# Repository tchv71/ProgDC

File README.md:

## Программируемый дешифратор (MMU) для Пальмиры

Прототипом послужил программируемый дешифратор для Радио 86-РК, описанный в журналах "Радио" 1994, №3-5. 

[https://archive.radio.ru/web/1994/03/020/]: https://archive.radio.ru/web/1994/03/020/

Общая идея конструктива - плата программируемого дешифратора вставляется в сокет процессора, а процессор (возможно, в виде z80card) вставляется в панельку на плате ПД. Дополнительные сигналы к/от платы Пальмиры выводятся на штырьковый разъем на правом краю платы ПД.

Внесены следующие усовершенствования:

1. Устранена зависимость от значений системного регистра при программировании устройства по адресу 0FFh. В оригинальном устройстве запись по адресу 0FFh меняла и значение системного регистра, и ОЗУ дешифратора. Это налагало ограничение на значения, которые можно записать в порт 0FFh и усложняло программирование. Теперь эти порты схемотехнически разделены - если было предварительное чтение из порта 0FFh, запись будет в системный регистр, в противном случае - в ОЗУ дешифратора.
2. Используются все биты ОЗУ дешифратора, старшие 4 бита используются для расширения адреса системного ОЗУ. Поддерживается до 512К системного ОЗУ. Поддерживается 64 (максимум 128) кбайта ПЗУ.
3. Бит 4 ОЗУ дешифратора более не используется как признак "только чтение", вместо него используется значение 3 номера линии устройства.
4. Поддерживается бит 0 байта расширения конфигурации Пальмиры, включающий теневое ОЗУ по адресам 0-7FFFh.
5. Поддерживается до 4-х конфигураций дешифратора, которые выбираются битами 4-3 системного регистра. Таким образом, для того, чтобы изменить конфигурацию памяти, нет необходимости менять её постранично, можно запрограммировать новую конфигурацию заранее, а потом мгновенно применить её одной запись в порт 0FFh.
6. Поддерживается процессор Z80 в формате z80-card. 580ВМ80А также поддерживается, совместно с системным контроллером 580ВК38
7. Вместо микросхемы КР537РУ10 применена IDC6116SA45P как более быстродействующая, изменены тайминги сигнала записи в нее для повышения надежности записи.

## Системный регистр (in/out 0FFh)

|Бит|Обозначение|Биты управления режимом|
|-|-|-|
|7|Q7|Работа|
|6|Q6|Программирование портов ввода-вывода|
|5|Q5|Программирование конфигурации памяти|
|4||Биты выбора конфигурации (запись) Бит1|
|3||Биты выбора конфигурации (запись) Бит0|
|2||Биты выбора конфигурации (чтение) Бит1|
|1||Биты выбора конфигурации (чтение) Бит0|
|0||свободно|

Чтобы записать в системный регистр, надо сначала из него прочитать. Первая запись после чтения по адресу 0FFh будет в системный регистр, все последующие - в ОЗУ дешифратора (в режиме программирования) или в порт в рабочем режиме.

## Назначение линий выхода дешифратора ИД3:

|Номер линии|Адрес в Пальмире|Устройство|
|-|-|-|
|0|0C200h|ВВ55 контроллер клавиатуры|
|1|0C400h|ВВ55 дополнительный контроллер|
|2|0C000h|ВГ75 контроллер дисплея|
|3|-|ОЗУ только чтение|
|4|0E000h|ПЗУ|
|5|0000h|ОЗУ первые 32кб|
|6|0CC00h|ВИ53-1|
|7|0C600h|ВТ57/ВТ37|
|8|0C800h|ВИ53-2|
|9|||
|10|0D800h|ОЗУ ЗГ РУ10|
|11|0CE00h|Palmira ext. byte|
|12|0C300h|FT245R port|
|13|8000h|ОЗУ вторые 32кб|
|14|0CA00h|VDP TMS9918A|
|15|0F700h|Страница контроллеров RK60k|

Линия 15 задает положения страницы контроллеров RK60k размером 256 байт. Контроллеры имеют следующие фиксированные относительные адреса:

|Номер|Контроллер|Адрес|
|-|-|-|
|0|FDC |0F700h; 1793 floppy disk controller|
|1|INTR|0F720h; 8259 interrupt controller   |
|2|PSG1|0F740h; 8253 first	                |
|3|PSG2|0F760h; 8253 second	      	        |
|4|PPI |0F780h; 8255 fist		                |
|5|PPI2|0F7A0h; 8255 second	            	  |
|6|DISP|0F7C0h; 8275 display adapter	      |
|7|DMA |0F7E0h; 8257 DMA chip	    	        |

Поскольку одна конфигурация занимает 512 байт в ОЗУ дешифратора, появляется возможность хранить 4 конфигурации и мгновенно переключать их битами 3 и 4 системного регистра.

## ПЗУ 556РТ4

| Бит адреса | Сигнал |
| ---------- | ------ |
| A3         | Q7     |
| A2         | Q6     |
| A1         | Q5     |
| A0         | In/Out |

## Ошибки в печатных платах:

### Версия 1.4:

1. На микросхему D10 6116SA45P не заведено питание и земля.
2. Вывод 8 В14.3 К555ЛА3 должен быть подключен к выводу 15 D9 КР556РТ4, а вывод 4 D9 - к земле.

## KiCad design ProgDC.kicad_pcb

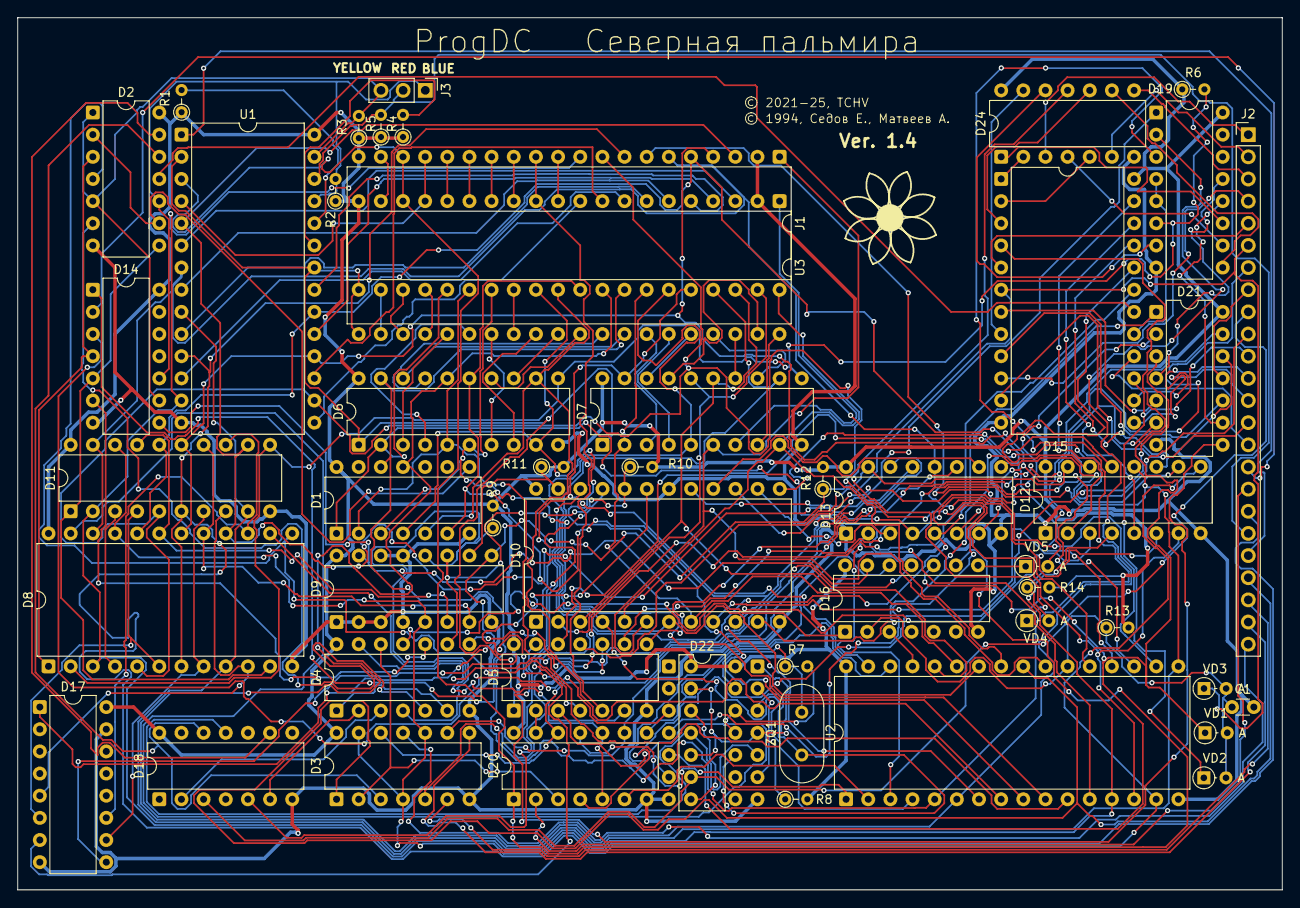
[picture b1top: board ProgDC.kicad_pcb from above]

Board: 2 copper layers, 145.0 x 100.0 mm, 51 parts (1 on the bottom side), 179 nets.

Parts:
C1: 470; C_Disc_D3.0mm_W1.6mm_P2.50mm
D1: K155LA2; DIP-14_W7.62mm
D2, D4, D16: 133LL1; DIP-14_W7.62mm
D3, D20, D24: 133LI1; DIP-14_W7.62mm
D5, D22: 133LN1; DIP-14_W7.62mm
D6, D7, D11: 1533ИР22; DIP-20_W7.62mm
D8: К589ИР12; DIP-24_W15.24mm
D9: КР556РТ4; DIP-16_W7.62mm
D10: КР537РУ10; DIP-24_W15.24mm
D12, D13: K589АП16; DIP-16_W7.62mm
D14: 133LA3; DIP-14_W7.62mm
D15: 155ID3; DIP-24_W15.24mm
D17: КР1533КП11; DIP-16_W7.62mm
D18, D23: 555TM2; DIP-14_W7.62mm
D19: 74AC138(COMB); DIP-16_W7.62mm
D21: 74HC86N; DIP-14_W7.62mm
J1: Conn_02x20_Counter_Clockwise_MountingPin; DIP-40_W15.24mm
J2: Conn_01x24_Pin; PinHeader_1x24_P2.54mm_Vertical
J3: Conn_01x03_Pin; PinHeader_1x03_P2.54mm_Vertical
R1, R2, R3, R4, R5, R6, R9, R10, R11, R12, R13, R14: R0125; R_Axial_DIN0204_L3.6mm_D1.6mm_P2.54mm_Vertical
R7, R8: R0125H; R_Axial_DIN0204_L3.6mm_D1.6mm_P2.54mm_Vertical
U1: KR580VK28; DIP-28_W15.24mm
U2: 628512; DIP-32_W15.24mm
U3: CPU; DIP-40_W15.24mm
VD1, VD2, VD3, VD4, VD5: 1N4148; D_DO-34_SOD68_P2.54mm_Vertical_AnodeUp
ZQ1: QUARTZ; Crystal_HC18-U_Vertical

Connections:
+5V: D1.14 (VCC), D2.14 (VCC), D3.14 (VCC), D4.14 (VCC), D5.14 (VCC), D6.20 (VCC), D7.20 (VCC), D8.24 (VCC), D9.16 (+5V), D10.24 (VCC), D11.20 (VCC), D12.16 (VCC), D13.16 (VCC), D14.14 (VCC), D15.24 (VCC), D16.14 (VCC), D17.16 (VCC), D18.14 (VCC), D19.16 (VCC), D20.14 (VCC), D21.14 (VCC), D22.14 (VCC), D23.14 (VCC), D24.14 (VCC), J1.20, R1.1 (TOP), R2.1 (TOP), R3.1 (TOP), R4.1 (TOP), R5.1 (TOP), R6.1 (TOP), R8.2, R9.2 (BOT), R10.2 (BOT), R11.2 (BOT), R12.2 (BOT), R13.2 (BOT), R14.2 (BOT), U1.28 (VCC), U2.32 (VCC), U3.20 (VCC)
/8MHZ: D18.11 (C), D23.5 (Q), D23.11 (C)
/"1": D6.11 (PE), D7.11 (PE), D8.2 (MD), D11.11 (PE), D19.6 (E1), R6.2 (BOT)
/+12V: J1.28, U3.28 (+12V)
/-5V: J1.11, U3.11 (-5V)
/A0: D6.3 (D0), U3.25 (A0)
/A1: D6.4 (D1), U3.26 (A1)
/A2: D6.7 (D2), U3.27 (A2)
/A3: D6.8 (D3), U3.29 (A3)
/A4: D6.13 (D4), U3.30 (A4)
/A5: D6.14 (D5), U3.31 (A5)
/A6: D6.17 (D6), U3.32 (A6)
/A7: D6.18 (D7), U3.33 (A7)
/A8: D7.3 (D0), U3.34 (A8)
/A9: D7.4 (D1), U3.35 (A9)
/A10: D7.7 (D2), U3.1 (A10)
/A11: D7.8 (D3), U3.40 (A11)
/A12: D7.13 (D4), U3.37 (A12)
/A13: D7.14 (D5), U3.38 (A13)
/A14: D7.17 (D6), U3.39 (A14)
/A15: D7.18 (D7), U3.36 (A15)
/AB0: D1.1, D6.2 (Q0), J1.25, U2.12 (A0)
/AB1: D1.2, D6.5 (Q1), J1.26, U2.11 (A1)
/AB2: D1.3, D6.6 (Q2), J1.27, U2.10 (A2)
/AB3: D1.4, D6.9 (Q3), J1.29, U2.9 (A3)
/AB4: D1.5, D6.12 (Q4), J1.30, U2.8 (A4)
/AB5: D1.6, D6.15 (Q5), D19.1 (0), J1.31, U2.7 (A5)
/AB6: D1.11, D6.16 (Q6), D19.2 (1), J1.32, U2.6 (A6)
/AB7: D1.12, D6.19 (Q7), D19.3 (2), J1.33, U2.5 (A7)
/AB8: D7.2 (Q0), D10.8 (A10), J1.34, U2.27 (A8)
/AB9: D7.5 (Q1), D10.7 (A9), J1.35, U2.26 (A9)
/AB10: D7.6 (Q2), D10.6 (A8), J1.1, U2.23 (A10)
/AB11: D7.9 (Q3), D10.5 (A7), J1.40, U2.25 (A11)
/AB12: D7.12 (Q4), D10.4 (A6), J1.37, U2.4 (A12)
/AB13: D7.15 (Q5), D10.3 (A5), J1.38, U2.28 (A13)
/AB14: D7.16 (Q6), D10.2 (A4), J1.39
/AB15: D7.19 (Q7), D10.1 (A3), J1.36, U2.31 (A15)
/ARR16: D20.6 (Y), U2.2 (A16)
/ARR17: D20.8 (Y), U2.30 (A17)
/ARR18: D20.11 (Y), U2.1 (A18)
/C1: J1.22, U3.22 (C1)
/C2: J1.15, U3.15 (C2)
/C800_VI53_2: D5.13 (A), D21.8 (Y)
/CLK: D18.3 (C), D23.9 (Q), J2.9
/CS_RAMR: D16.12 (A), D22.6 (Y)
/D0: U1.15 (D0), U3.10 (D0)
/D1: U1.17 (D1), U3.9 (D1)
/D2: U1.12 (D2), U3.8 (D2)
/D3: U1.10 (D3), U3.7 (D3)
/D4: U1.6 (D4), U3.3 (D4)
/D5: U1.19 (D5), U3.4 (D5)
/D6: U1.21 (D6), U3.5 (D6)
/D7: U1.8 (D7), U3.6 (D7)
/DB0: D8.3 (D0), D11.2 (Q0), D12.4 (DI0), J1.10, U1.13 (DB0), U2.13 (D0)
/DB1: D8.5 (D1), D11.5 (Q1), D12.7 (DI1), J1.9, U1.16 (DB1), U2.14 (D1)
/DB2: D8.7 (D2), D11.6 (Q2), D12.9 (DI2), J1.8, U1.11 (DB2), U2.15 (D2)
/DB3: D8.9 (D3), D11.9 (Q3), D12.12 (DI3), J1.7, U1.9 (DB3), U2.17 (D3)
/DB4: D8.16 (D4), D11.12 (Q4), D13.4 (DI0), J1.3, U1.5 (DB4), U2.18 (D4)
/DB5: D8.18 (D5), D11.15 (Q5), D13.7 (DI1), J1.4, U1.18 (DB5), U2.19 (D5)
/DB6: D8.20 (D6), D11.16 (Q6), D13.9 (DI2), J1.5, U1.20 (DB6), U2.20 (D6)
/DB7: D8.22 (D7), D11.19 (Q7), D13.12 (DI3), J1.6, U1.7 (DB7), U2.21 (D7)
/DBIN: J1.17, U1.4 (DBIN), U3.17 (RC)
/HLD: J1.13, U3.13 (HLD)
/HLDA: D5.1 (A), D6.1 (~EO), D7.1 (~EO), J1.21, U1.2 (HLDA), U1.22 (BUSEN), U3.21 (HLDA)
/INT: J1.14, U3.14 (INT)
/INTE: J1.16, U3.16 (INTE)
/P0: D4.4 (A), D9.12 (D0), R9.1 (TOP)
/P1: D4.9 (A), D9.11 (D1), D10.20 (~OE), R10.1 (TOP)
/P2: D9.10 (D2), D10.23 (A2), R11.1 (TOP)
/P3: D9.9 (D3), D12.15 (~CE), D13.15 (~CE), D17.1 (SEL), R12.1 (TOP)
/Q0: D8.4 (Q0), D11.3 (D0)
/Q1: D8.6 (Q1), D11.4 (D1), D17.6 (2B)
/Q2: D8.8 (Q2), D11.7 (D2), D17.10 (3B)
/Q3: D8.10 (Q3), D11.8 (D3), D17.5 (2A)
/Q4: D8.15 (Q4), D11.13 (D4), D17.11 (3A)
/Q5: D8.17 (Q5), D9.7 (A2), D11.14 (D5)
/Q6: D8.19 (Q6), D9.6 (A1), D11.17 (D6)
/Q7: D3.4 (A), D3.10 (B), D3.13 (B), D8.21 (Q7), D9.5 (A0), D11.18 (D7), J2.18
/R0: D12.2 (DO0), D15.23 (1)
/R1: D12.5 (DO1), D15.22 (2)
/R2: D12.11 (DO2), D15.21 (4)
/R3: D12.14 (DO3), D15.20 (8)
/R4: D13.2 (DO0), U2.3 (A14)
/R5: D3.5 (B), D13.5 (DO1), D21.1 (A)
/R6: D3.9 (A), D13.11 (DO2), D20.9 (A)
/R7: D3.12 (A), D13.14 (DO3), D20.12 (A)
/R8: D14.3 (Y), D22.3 (A)
/RAM_SEL: D14.2 (B), J2.16
/RDY: J1.23, U3.23 (RDY)
/RESET: D5.5 (A), J1.12, U3.12 (RST)
/ROM_A13: D3.6 (Y), J2.22
/ROM_A14: D3.8 (Y), J2.23
/ROM_A15: D3.11 (Y), J2.24
/STSTB: J2.20, U1.1 (STSTB)
/SYN: J1.19, U3.19 (SYN)
/WI: J1.24, U3.24 (WI)
/~A_FF: D1.8, D2.2 (B), D2.9 (A)
/~C100_SD_CNTR: D15.10 (9), J2.4
/~C200_PPI1_: D24.3 (Y), J2.1
/~C200_PPI1: D15.1 (0), D24.2 (B)
/~C300: D15.14 (12), J2.13
/~C400_PPI2_: D24.6 (Y), J2.2
/~C400_PPI2: D15.2 (1), D24.5 (B)
/~C500_VDP: D15.16 (14), J2.15
/~C800_VI53_2_: D5.12 (Y), J2.10
/~C800_VI53_2: D15.9 (8), D21.10 (B)
/~CC00_VI53_1_: D5.8 (Y), J2.7
/~CC00_VI53_1: D15.7 (6), D21.5 (B)
/~CE00: D15.13 (11), J2.12
/~CS_628512: C1.1, D16.2 (B), R13.1 (TOP), U2.22 (CS), VD1.2 (A), VD2.2 (A), VD3.2 (A)
/~CS_D800: D15.11 (10), J2.14
/~CS_DMA_2: D21.11 (Y), J2.8
/~CS_DMA_: D24.11 (Y), VD4.1 (K)
/~CS_DMA: D15.8 (7), D24.13 (B)
/~CS_RAMR: D15.4 (3), D16.10 (B), D22.5 (A), VD1.1 (K)
/~CS_ROM: D15.5 (4), J2.5
/~CS_SRAM_8000: D15.15 (13), J2.11, VD2.1 (K)
/~CS_VG75_: D24.8 (Y), J2.3
/~CS_VG75: D15.3 (2), D24.10 (B)
/~D15_CS1: D4.8 (Y), D15.19 (&C)
/~D15_CS2: D2.11 (Y), D15.18 (C)
/~F700: D15.17 (15), D19.4 (~E2), D19.5 (~E3)
/~INTA: R4.2 (BOT), U1.23 (INTA)
/~I/OR: D2.10 (B), D14.10 (B), J3.1, R2.2 (BOT), U1.25 (I/OR)
/~I/OW: D2.1 (A), D2.5 (B), D14.9 (A), J3.3, R3.2 (BOT), U1.27 (I/OW)
/~MEMR: R1.2 (BOT), U1.24 (MEMR)
/~MEMW_VT57: D20.2 (B), J2.17
/~MEMW: J2.19, J3.2, R5.2 (BOT), U1.26 (MEMW)
/~MWR: D3.2 (B), D4.12 (A), D20.3 (Y)
/~RAM_MAIN: D5.11 (A), D15.6 (5), J2.6, VD3.1 (K)
/~RD: D3.1 (A), J2.21, U2.24 (RD)
/~RESET: D5.6 (Y), D8.14 (RES)
/~WE_628512: D4.11 (Y), D16.1 (A)
/~WR: D16.9 (A), D20.1 (A), J1.18, U1.3 (WR), U3.18 (TR)
GND: C1.2, D1.7 (GND), D2.7 (GND), D3.7 (GND), D4.7 (GND), D5.7 (GND), D6.10 (GND), D7.10 (GND), D8.12 (GND), D9.1 (A6), D9.2 (A5), D9.3 (A4), D9.4 (A3), D9.8 (GND), D9.13 (~CS1), D9.14 (~CS2), D10.12 (GND), D10.18 (~CS), D11.10 (GND), D12.1 (~CS), D12.8 (GND), D13.1 (~CS), D13.8 (GND), D14.7 (GND), D15.12 (GND), D16.7 (GND), D17.8 (GND), D17.15 (~OE), D18.7 (GND), D19.8 (GND), D20.7 (GND), D21.7 (GND), D21.12 (A), D22.7 (GND), D23.7 (GND), D24.7 (GND), J1.2, U1.14 (GND), U2.16 (GND), U3.2 (GND)
unnamed: D2.4 (A), D5.4 (Y), D8.13 (CS2)
unnamed: D2.6 (Y), D4.5 (B)
unnamed: D4.1 (A), D4.6 (Y)
unnamed: D5.3 (A), D8.23 (S1)
unnamed: D10.19 (A0), D17.9 (3Y)
unnamed: D10.22 (A1), D17.7 (2Y)
unnamed: D10.9 (D0), D12.3 (DB0)
unnamed: D10.10 (D1), D12.6 (DB1)
unnamed: D10.11 (D2), D12.10 (DB2)
unnamed: D10.13 (D3), D12.13 (DB3)
unnamed: D10.14 (D4), D13.3 (DB0)
unnamed: D10.15 (D5), D13.6 (DB1)
unnamed: D10.16 (D6), D13.10 (DB2)
unnamed: D10.17 (D7), D13.13 (DB3)
unnamed: D10.21 (~WE), D18.5 (Q)
unnamed: D2.8 (Y), D8.11 (EV), D11.1 (~EO), D14.5 (B)
unnamed: D5.10 (Y), D14.1 (A)
unnamed: D2.3 (Y), D8.1 (CS1), D14.4 (A)
unnamed: D4.10 (B), D14.6 (Y)
unnamed: D9.15 (A7), D14.8 (Y), D16.13 (B)
unnamed: D16.3 (Y), U2.29 (WR)
unnamed: D16.8 (Y), VD5.1 (K)
unnamed: D4.13 (B), D16.11 (Y)
unnamed: D4.3 (Y), D18.2 (D)
unnamed: D4.2 (B), D18.6 (~Q)
unnamed: D2.12 (A), D3.3 (Y), D18.12 (D)
unnamed: D2.13 (B), D18.9 (Q)
unnamed: D19.12 (3), D21.9 (A)
unnamed: D19.11 (4), D24.1 (A)
unnamed: D19.10 (5), D24.4 (A)
unnamed: D19.9 (6), D24.9 (A)
unnamed: D20.4 (A), D21.3 (Y)
unnamed: D5.2 (Y), D20.5 (B), D20.10 (B), D20.13 (B)
unnamed: D21.2 (B), D22.4 (Y)
unnamed: D19.13 (2), D21.4 (A)
unnamed: D5.9 (A), D21.6 (Y)
unnamed: D21.13 (B), R14.1 (TOP), VD4.2 (A), VD5.2 (A)
unnamed: D22.11 (A), D22.12 (Y), R7.2
unnamed: D22.10 (Y), D23.3 (C), ZQ1.1
unnamed: D22.13 (A), R7.1, ZQ1.2
unnamed: D23.2 (D), D23.6 (~Q)
unnamed: D23.1 (~R), D23.4 (~S), D23.10 (~S), D23.13 (~R)
unnamed: D23.8 (~Q), D23.12 (D)
unnamed: D19.7, D24.12 (A)

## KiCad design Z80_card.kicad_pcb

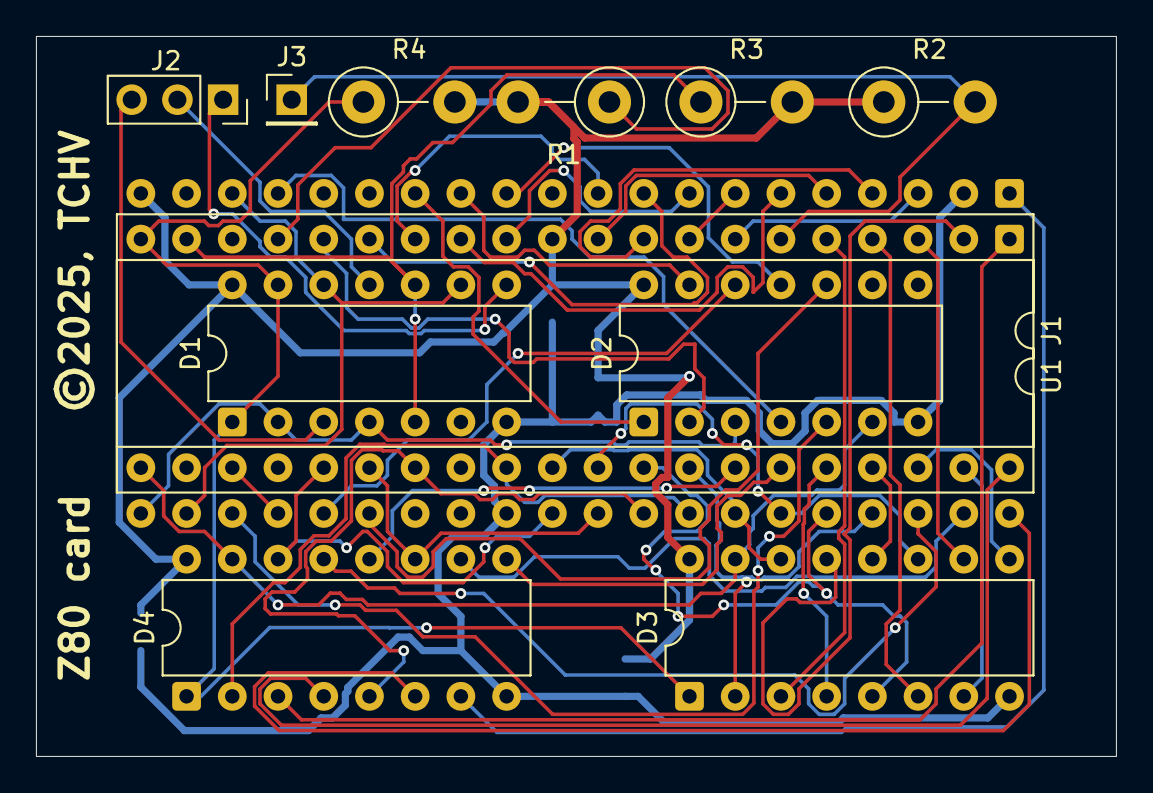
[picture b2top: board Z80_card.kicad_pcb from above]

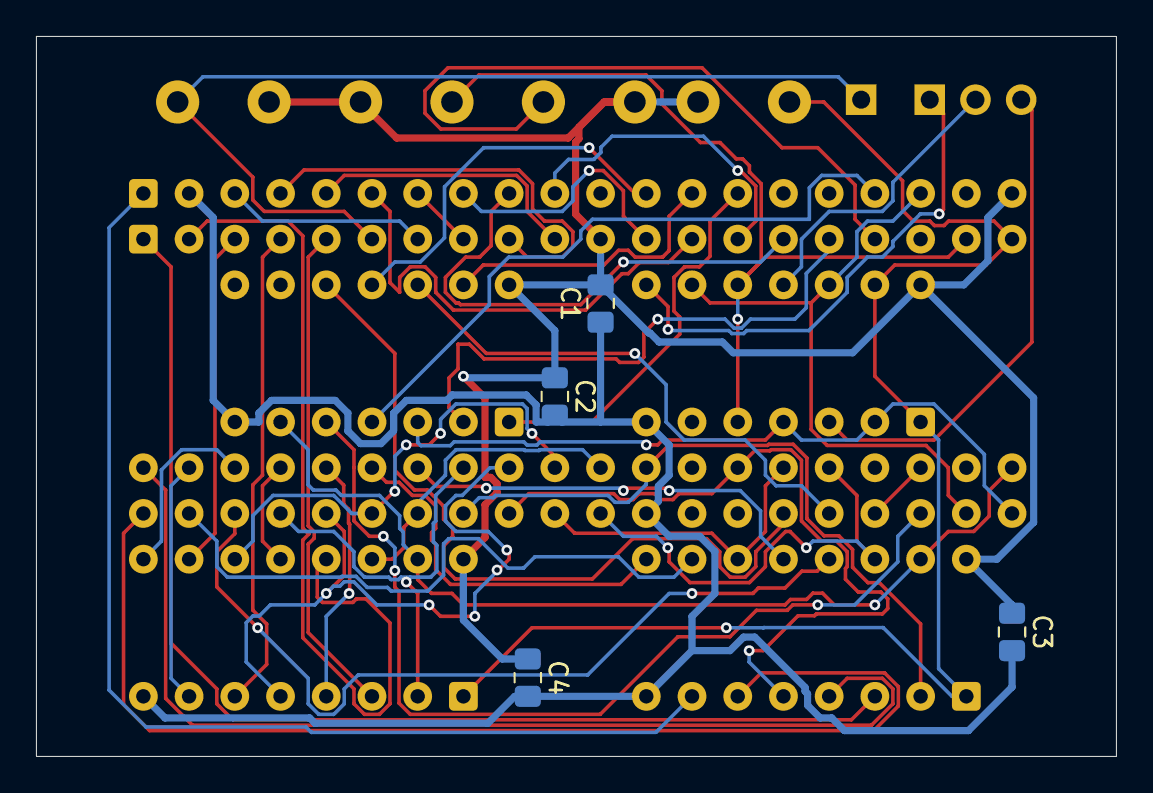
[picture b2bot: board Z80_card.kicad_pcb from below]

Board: 2 copper layers, 60.0 x 40.0 mm, 16 parts (4 on the bottom side), 53 nets.

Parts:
C1, C2, C3, C4: C; C_0805_2012Metric_Pad1.18x1.45mm_HandSolder
D1: 133LL1; DIP-14_W7.62mm
D2: 133LN1; DIP-14_W7.62mm
D3, D4: КР1533КП11; DIP-16_W7.62mm
J1: Conn_02x20_Counter_Clockwise_MountingPin; DIP-40_W15.24mm
J2: Conn_01x03_Pin; PinSocket_1x03_P2.54mm_Vertical
J3: Conn_01x01_Pin; PinHeader_1x01_P2.54mm_Vertical
R1, R2, R3, R4: R0125; R_Axial_DIN0411_L9.9mm_D3.6mm_P5.08mm_Vertical
U1: Z84C00-4SC; DIP-40_W15.24mm

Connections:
+5V: C1.2, C2.1, C3.1, C4.1, D1.14 (VCC), D2.14 (VCC), D3.16 (VCC), D4.16 (VCC), J1.20, R1.2 (BOT), R2.1 (TOP), R3.2 (BOT), R4.2 (BOT), U1.11 (VCC)
/A0: D4.14 (4A), J1.25, U1.30 (A0)
/A1: D4.11 (3A), J1.26, U1.31 (A1)
/A2: D4.5 (2A), J1.27, U1.32 (A2)
/A3: D4.2 (1A), J1.29, U1.33 (A3)
/A4: D3.14 (4A), J1.30, U1.34 (A4)
/A5: D3.11 (3A), J1.31, U1.35 (A5)
/A6: D3.5 (2A), J1.32, U1.36 (A6)
/A7: D3.2 (1A), J1.33, U1.37 (A7)
/A8: D4.12 (4Y), J1.34
/A9: D4.9 (3Y), J1.35
/A10: D4.7 (2Y), J1.1
/A11: D4.4 (1Y), J1.40
/A12: D3.12 (4Y), J1.37
/A13: D3.9 (3Y), J1.38
/A14: D3.7 (2Y), J1.39
/A15: D3.4 (1Y), J1.36
/BLUE: D1.3 (Y), J2.3
/CLK: J3.1, R2.2 (BOT), U1.6 (CLK)
/D0: J1.10, U1.14 (D0)
/D1: J1.9, U1.15 (D1)
/D2: J1.8, U1.12 (D2)
/D3: J1.7, U1.8 (D3)
/D4: J1.3, U1.7 (D4)
/D5: J1.4, U1.9 (D5)
/D6: J1.5, U1.10 (D6)
/D7: J1.6, U1.13 (D7)
/DBIN: D2.4 (Y), J1.17
/HLD: D2.13 (A), J1.13
/INT: D2.1 (A), J1.14
/RDY: J1.23, U1.24 (~WAIT)
/RED: D1.8 (Y), J2.1
/RESET: D2.11 (A), J1.12
/YELLOW: D1.11 (Y), J2.2
/_A8: D4.13 (4B), U1.38 (A8)
/_A9: D4.10 (3B), U1.39 (A9)
/_A10: D4.6 (2B), U1.40 (A10)
/_A11: D4.3 (1B), U1.1 (A11)
/_A12: D3.13 (4B), U1.2 (A12)
/_A13: D3.10 (3B), U1.3 (A13)
/_A14: D3.6 (2B), U1.4 (A14)
/_A15: D3.3 (1B), U1.5 (A15)
/_HLDA: D2.6 (Y), D3.15 (~OE), D4.15 (~OE), J1.21
/~RESET: D2.10 (Y), U1.26 (~RESET)
/~WR: D1.9 (A), D1.12 (A), J1.18, U1.22 (~WR)
GND: C1.1, C2.2, C3.2, C4.2, D1.7 (GND), D2.7 (GND), D3.8 (GND), D4.8 (GND), J1.2, U1.29 (GND)
unnamed: D1.1 (A), D1.13 (B), D3.1 (SEL), D4.1 (SEL), R4.1 (TOP), U1.20 (~IORQ)
unnamed: D1.2 (B), D1.4 (A), D2.3 (A), U1.21 (~RD)
unnamed: D1.5 (B), D1.10 (B), R3.1 (TOP), U1.19 (~MREQ)
unnamed: D2.2 (Y), U1.16 (~INT)
unnamed: D2.5 (A), U1.23 (~BUSACK)
unnamed: D2.12 (Y), U1.25 (~BUSREQ)
unnamed: R1.1 (TOP), U1.17 (~NMI)

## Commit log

2025-04-29 Fix address and data buffering
2025-05-01 Ver. 1.4
2025-05-27 Fix layout
2026-02-05 Update PCB
2026-02-06 Fix pcb
2026-03-20 Fix bugs
2026-03-25 Add rom table into read.me
2026-04-02 Add PSG select

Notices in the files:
ProgDC.kicad_pcb:
© 2021-25, TCHV
© 1994, Седов Е., Матвеев А.
Z80_card.kicad_pcb:
Z80 card ©2025, TCHV
